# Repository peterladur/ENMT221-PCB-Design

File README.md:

# ENMT221-PCB-Design
PCB Design for my line following robot for ENMT221

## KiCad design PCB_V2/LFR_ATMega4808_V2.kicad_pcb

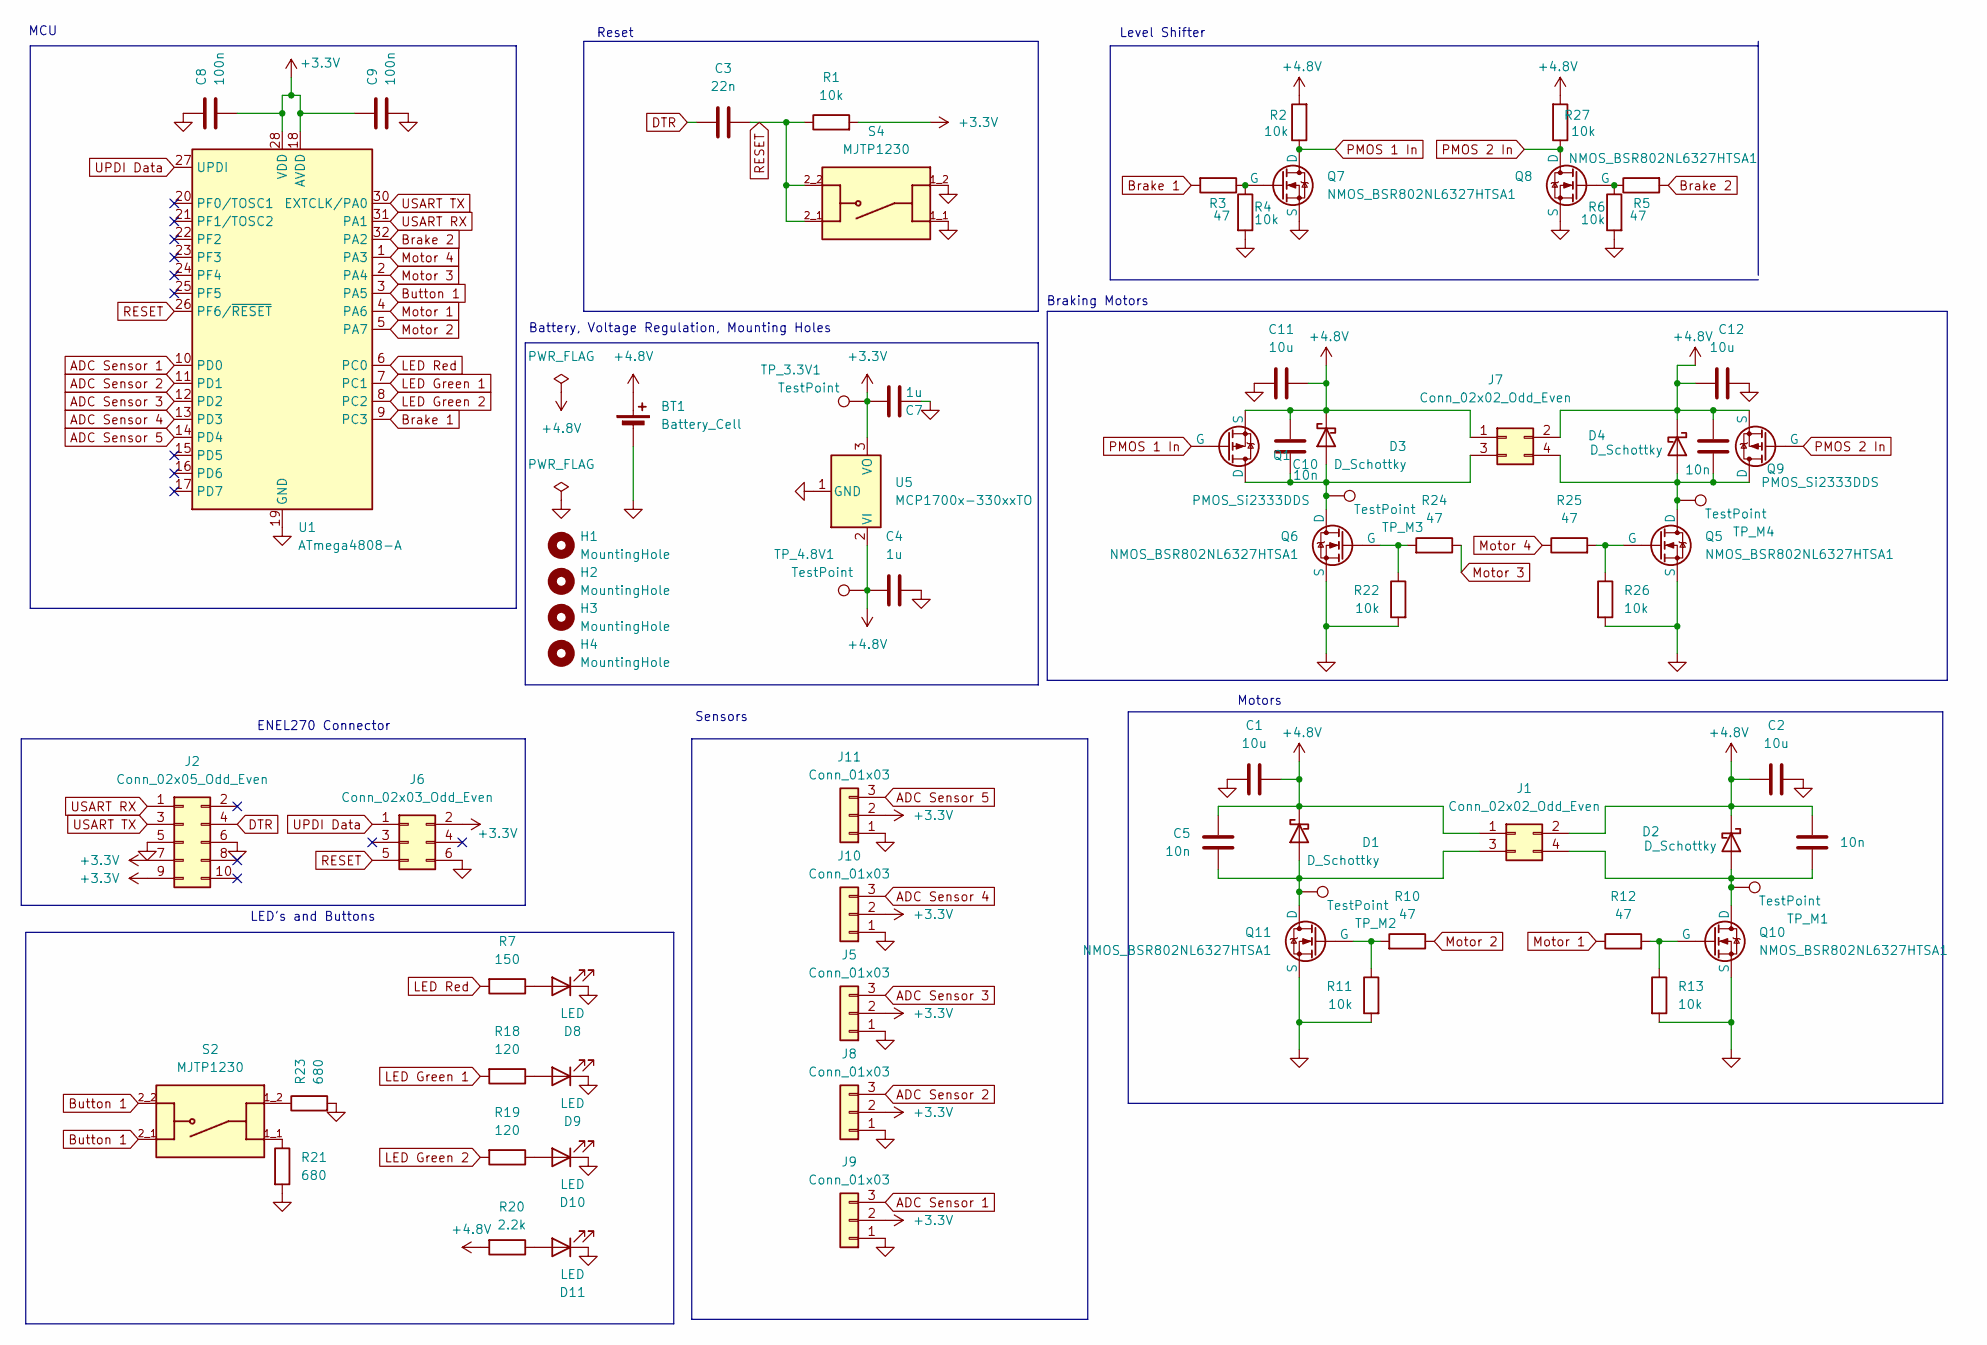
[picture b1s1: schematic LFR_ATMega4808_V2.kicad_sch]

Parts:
BT1: Battery_Cell; PinHeader_1x02_P2.54mm_Vertical
C1, C2, C11, C12: 10u; C_Radial_D6.3mm_H5.0mm_P2.50mm
C3: 22n; C_0805_2012Metric_Pad1.18x1.45mm_HandSolder
C4, C7: 1u; C_Radial_D6.3mm_H5.0mm_P2.50mm
C5, C6, C10, C13: 10n; C_0805_2012Metric_Pad1.18x1.45mm_HandSolder
C8, C9: 100n; C_0805_2012Metric_Pad1.18x1.45mm_HandSolder
D1, D2, D3, D4: D_Schottky; D_SMA
D8, D9, D10, D11: LED; LED_D5.0mm
H1, H2, H3, H4: MountingHole; MountingHole_2.2mm_M2_Pad
J1, J7: Conn_02x02_Odd_Even; PinHeader_2x02_P2.54mm_Vertical
J2: Conn_02x05_Odd_Even; PinHeader_2x05_P2.54mm_Vertical
J5, J8, J9, J10, J11: Conn_01x03; PinHeader_1x03_P2.54mm_Vertical
J6: Conn_02x03_Odd_Even; PinHeader_2x03_P2.54mm_Vertical
Q1: PMOS_Si2333DDS; SOT-23-3
Q5, Q6, Q7, Q8, Q10, Q11: NMOS_BSR802NL6327HTSA1; SOT-23-3
Q9: PMOS_Si2333DDS; SOT-23
R1, R2, R4, R6, R11, R13, R22, R26, R27: 10k; R_0805_2012Metric_Pad1.20x1.40mm_HandSolder
R3, R5, R10, R12, R24, R25: 47; R_0805_2012Metric_Pad1.20x1.40mm_HandSolder
R7: 150; R_0805_2012Metric_Pad1.20x1.40mm_HandSolder
R18, R19: 120; R_0805_2012Metric_Pad1.20x1.40mm_HandSolder
R20: 2.2k; R_0805_2012Metric_Pad1.20x1.40mm_HandSolder
R21, R23: 680; R_0805_2012Metric_Pad1.20x1.40mm_HandSolder
S2, S4: MJTP1230; Switch_Tactile_THT_6x6mm_MJTP1230; PARTREV NA
TP_3.3V1, TP_4.8V1: TestPoint; TestPoint_Pad_D1.0mm
TP_M1, TP_M2, TP_M3, TP_M4: TestPoint; TestPoint_Pad_D1.0mm
U1: ATmega4808-A; TQFP-32_7x7mm_P0.8mm
U5: MCP1700x-330xxTO; TO-92_Inline

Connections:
+3.3V: C7.1, C8.2, C9.1, J2.7, J2.9, J5.2, J6.2, J8.2, J9.2, J10.2, J11.2, R1.2, TP_3.3V1.1 (1_1), U1.18 (AVDD), U1.28 (VDD), U5.3 (VO)
+4.8V: BT1.1 (+), C1.2, C2.2, C4.1, C5.1, C6.1, C10.1, C11.2, C12.2, C13.1, D1.1 (K), D2.1 (K), D3.1 (K), D4.1 (K), J1.1, J1.2, J7.1, J7.2, Q1.2 (S), Q9.2 (S), R2.2, R20.2, R27.2, TP_4.8V1.1 (1_1), U5.2 (VI)
ADC Sensor 1: J9.3, U1.10 (PD0)
ADC Sensor 2: J8.3, U1.11 (PD1)
ADC Sensor 3: J5.3, U1.12 (PD2)
ADC Sensor 4: J10.3, U1.13 (PD3)
ADC Sensor 5: J11.3, U1.14 (PD4)
Brake 1: R3.2, U1.9 (PC3)
Brake 2: R5.2, U1.32 (PA2)
Button 1: S2.2_1, S2.2_2, U1.3 (PA5)
DTR: C3.1, J2.4
GND: BT1.2 (-), C1.1, C2.1, C4.2, C7.2, C8.1, C9.2, C11.1, C12.1, D8.1 (K), D9.1 (K), D10.1 (K), D11.1 (K), J2.5, J2.6, J5.1, J6.6, J8.1, J9.1, J10.1, J11.1, Q5.2 (S), Q6.2 (S), Q7.2 (S), Q8.2 (S), Q10.2 (S), Q11.2 (S), R4.2, R6.2, R11.2, R13.2, R21.2, R22.2, R23.2, R26.2, S4.1_1, S4.1_2, U1.19 (GND), U1.29 (GND), U5.1 (GND)
LED Green 1: R18.2, U1.7 (PC1)
LED Green 2: R19.2, U1.8 (PC2)
LED Red: R7.2, U1.6 (PC0)
Motor 1: R12.1, U1.4 (PA6)
Motor 2: R10.1, U1.5 (PA7)
Motor 3: R24.1, U1.2 (PA4)
Motor 4: R25.1, U1.1 (PA3)
unnamed: C5.2, D1.2 (A), J1.3, Q11.3 (D), TP_M2.1 (1_1)
unnamed: C6.2, D2.2 (A), J1.4, Q10.3 (D), TP_M1.1 (1_1)
unnamed: C10.2, D3.2 (A), J7.3, Q1.3 (D), Q6.3 (D), TP_M3.1 (1_1)
unnamed: C13.2, D4.2 (A), J7.4, Q5.3 (D), Q9.3 (D), TP_M4.1 (1_1)
unnamed: D8.2 (A), R7.1
unnamed: D9.2 (A), R18.1
unnamed: D10.2 (A), R19.1
unnamed: D11.2 (A), R20.1
unnamed: Q5.1 (G), R25.2, R26.1
unnamed: Q6.1 (G), R22.1, R24.2
unnamed: Q7.1 (G), R3.1, R4.1
unnamed: Q8.1 (G), R5.1, R6.1
unnamed: Q10.1 (G), R12.2, R13.1
unnamed: Q11.1 (G), R10.2, R11.1
unnamed: R21.1, S2.1_1
unnamed: R23.1, S2.1_2
PMOS 1 In: Q1.1 (G), Q7.3 (D), R2.1
PMOS 2 In: Q8.3 (D), Q9.1 (G), R27.1
RESET: C3.2, J6.5, R1.1, S4.2_1, S4.2_2, U1.26 (PF6/~RESET)
UPDI Data: J6.1, U1.27 (UPDI)
USART RX: J2.1, U1.31 (PA1)
USART TX: J2.3, U1.30 (EXTCLK/PA0)

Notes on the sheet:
LED's and Buttons
Level Shifter
ENEL270 Connector
MCU
Battery, Voltage Regulation, Mounting Holes
Reset
Sensors
Motors
Braking Motors

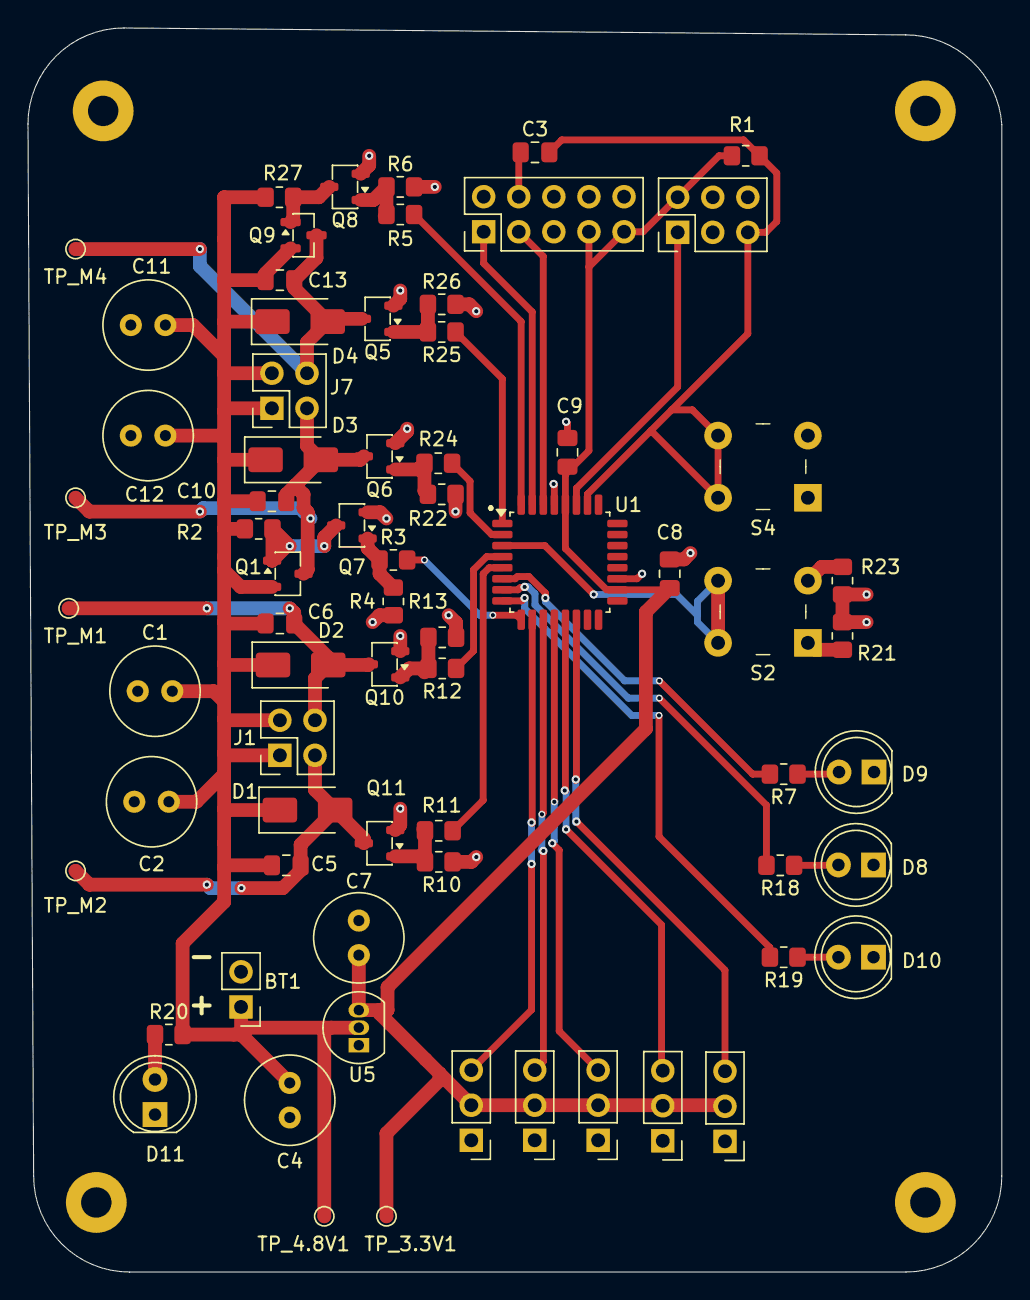
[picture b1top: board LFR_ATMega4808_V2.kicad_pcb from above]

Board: 2 copper layers, 70.5 x 90.0 mm, 74 parts (0 on the bottom side), 41 nets.

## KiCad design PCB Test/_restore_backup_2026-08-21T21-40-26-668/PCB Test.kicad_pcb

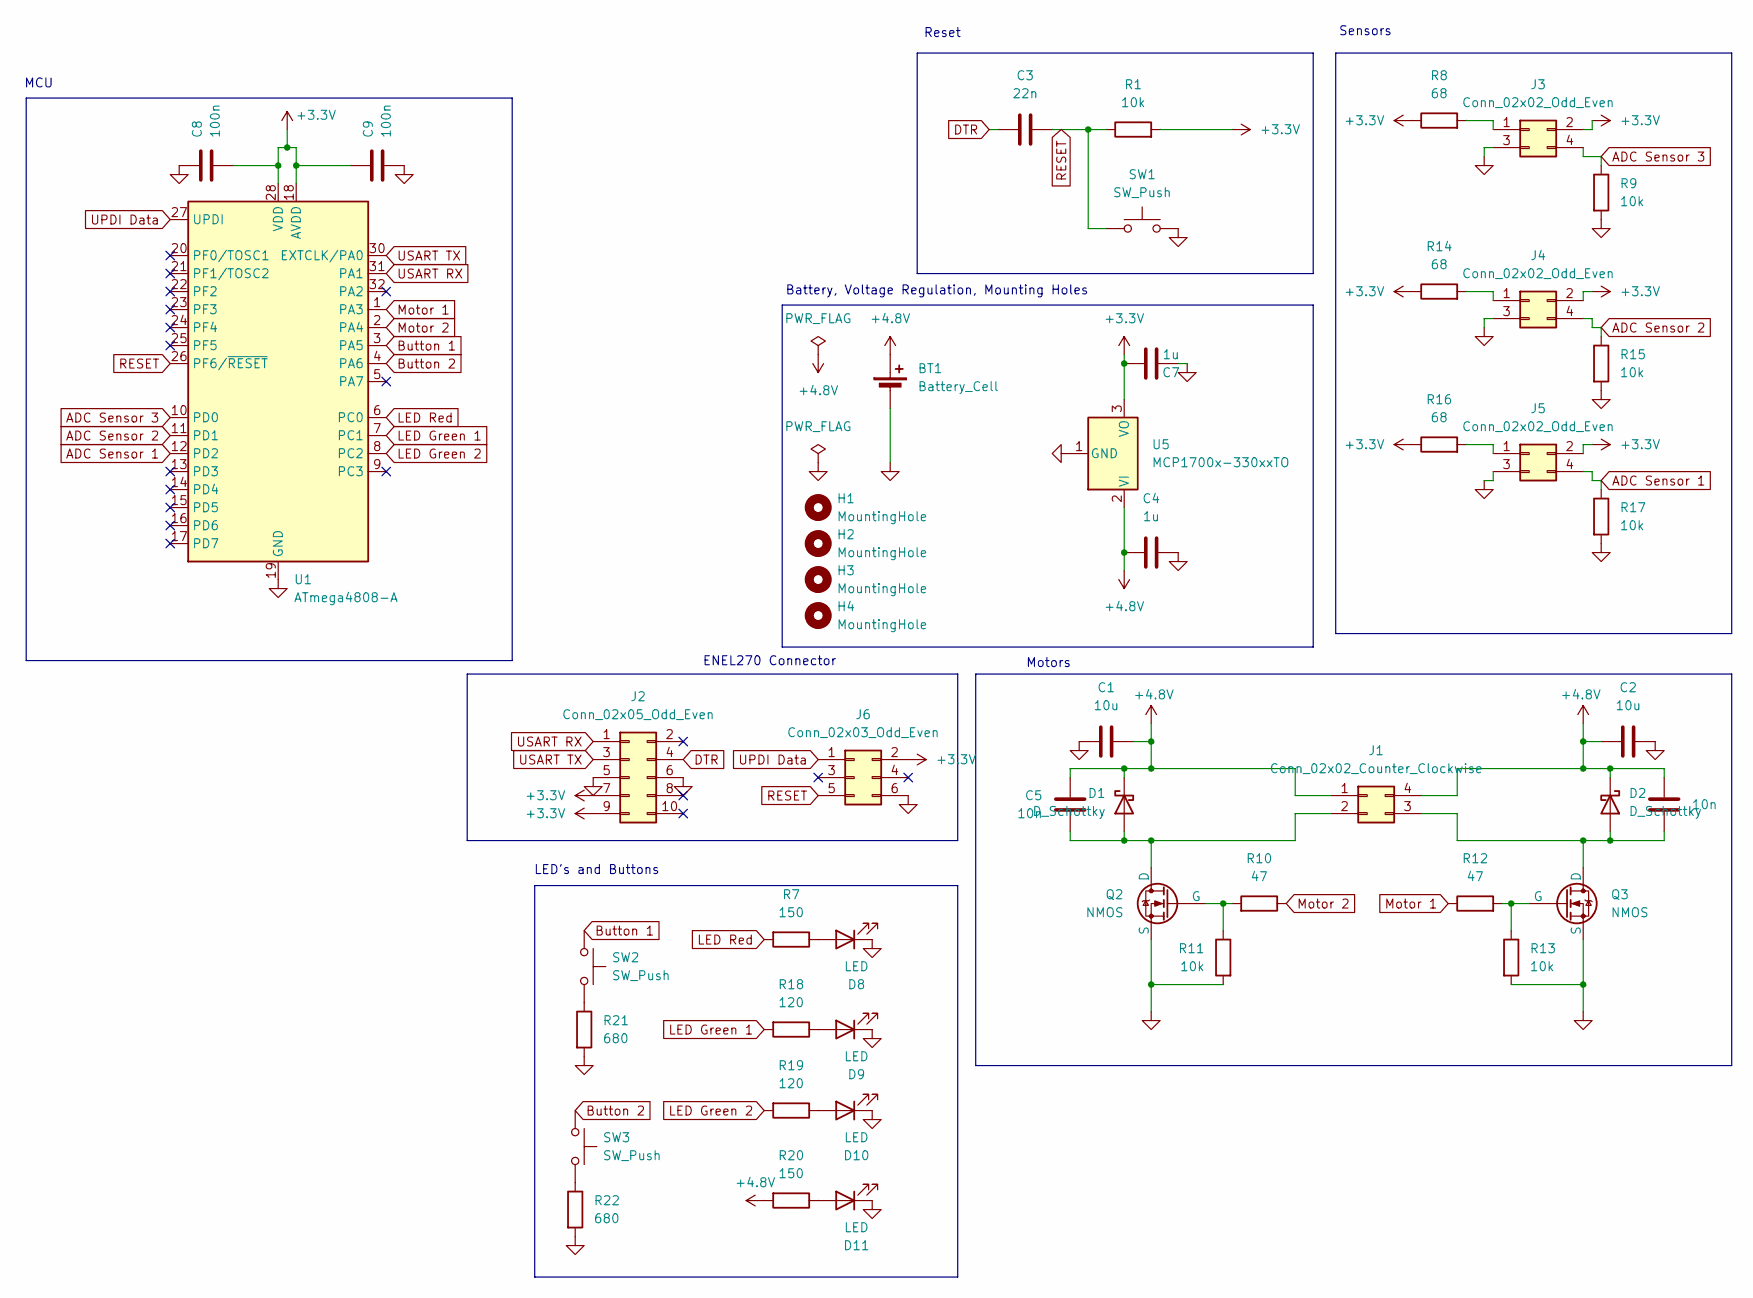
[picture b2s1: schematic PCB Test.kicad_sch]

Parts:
BT1: Battery_Cell; PinSocket_1x02_P1.00mm_Vertical_SMD_Pin1Left
C1, C2: 10u; C_Radial_D6.3mm_H5.0mm_P2.50mm
C3: 22n; C_0805_2012Metric_Pad1.18x1.45mm_HandSolder
C4, C7: 1u; C_Radial_D6.3mm_H5.0mm_P2.50mm
C5, C6: 10n; C_0805_2012Metric_Pad1.18x1.45mm_HandSolder
C8, C9: 100n; C_0805_2012Metric_Pad1.18x1.45mm_HandSolder
D1, D2: D_Schottky; D_SMA
D8, D9, D10, D11: LED; LED_D5.0mm
H1, H2, H3, H4: MountingHole; MountingHole_2.2mm_M2
J1: Conn_02x02_Counter_Clockwise; NS-Tech_Grove_1x04_P2mm_Vertical
J2: Conn_02x05_Odd_Even; PinHeader_2x05_P2.54mm_Vertical
J3, J4, J5: Conn_02x02_Odd_Even; Harwin_LTek-Male_2x02_P2.00mm_Vertical
J6: Conn_02x03_Odd_Even; PinHeader_2x03_P2.54mm_Vertical
Q2, Q3: NMOS; SOT-23
R1, R9, R11, R13, R15, R17: 10k; R_0805_2012Metric_Pad1.20x1.40mm_HandSolder
R7, R20: 150; R_0805_2012Metric_Pad1.20x1.40mm_HandSolder
R8, R14, R16: 68; R_0805_2012Metric_Pad1.20x1.40mm_HandSolder
R10, R12: 47; R_0805_2012Metric_Pad1.20x1.40mm_HandSolder
R18, R19: 120; R_0805_2012Metric_Pad1.20x1.40mm_HandSolder
R21, R22: 680; R_0805_2012Metric_Pad1.20x1.40mm_HandSolder
SW1, SW2, SW3: SW_Push; SW_PUSH_1P1T_6x3.5mm_H4.3_APEM_MJTP1243
U1: ATmega4808-A; TQFP-32_7x7mm_P0.8mm
U5: MCP1700x-330xxTO; TO-92_Inline

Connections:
+3.3V: C7.1, C8.2, C9.1, J2.7, J2.9, J3.2, J4.2, J5.2, J6.2, R1.2, R8.1, R14.1, R16.1, U1.18 (AVDD), U1.28 (VDD), U5.3 (VO)
+4.8V: BT1.1 (+), C1.2, C2.2, C4.1, C5.1, C6.1, D1.1 (K), D2.1 (K), J1.1, J1.4, R20.2, U5.2 (VI)
ADC Sensor 1: J5.4, R17.1, U1.12 (PD2)
ADC Sensor 2: J4.4, R15.1, U1.11 (PD1)
ADC Sensor 3: J3.4, R9.1, U1.10 (PD0)
Button 1: SW2.1, U1.3 (PA5)
Button 2: SW3.1, U1.4 (PA6)
DTR: C3.1, J2.4
GND: BT1.2 (-), C1.1, C2.1, C4.2, C7.2, C8.1, C9.2, D8.1 (K), D9.1 (K), D10.1 (K), D11.1 (K), J2.5, J2.6, J3.3, J4.3, J5.3, J6.6, Q2.3 (S), Q3.3 (S), R9.2, R11.2, R13.2, R15.2, R17.2, R21.2, R22.2, SW1.2, U1.19 (GND), U1.29 (GND), U5.1 (GND)
LED Green 1: R18.2, U1.7 (PC1)
LED Green 2: R19.2, U1.8 (PC2)
LED Red: R7.2, U1.6 (PC0)
Motor 1: R12.1, U1.1 (PA3)
Motor 2: R10.1, U1.2 (PA4)
unnamed: C5.2, D1.2 (A), J1.2, Q2.1 (D)
unnamed: C6.2, D2.2 (A), J1.3, Q3.1 (D)
unnamed: D8.2 (A), R7.1
unnamed: D9.2 (A), R18.1
unnamed: D10.2 (A), R19.1
unnamed: D11.2 (A), R20.1
unnamed: J3.1, R8.2
unnamed: J4.1, R14.2
unnamed: J5.1, R16.2
unnamed: Q2.2 (G), R10.2, R11.1
unnamed: Q3.2 (G), R12.2, R13.1
unnamed: R21.1, SW2.2
unnamed: R22.1, SW3.2
RESET: C3.2, J6.5, R1.1, SW1.1, U1.26 (PF6/~RESET)
UPDI Data: J6.1, U1.27 (UPDI)
USART RX: J2.1, U1.31 (PA1)
USART TX: J2.3, U1.30 (EXTCLK/PA0)

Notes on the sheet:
LED's and Buttons
ENEL270 Connector
MCU
Battery, Voltage Regulation, Mounting Holes
Reset
Sensors
Motors

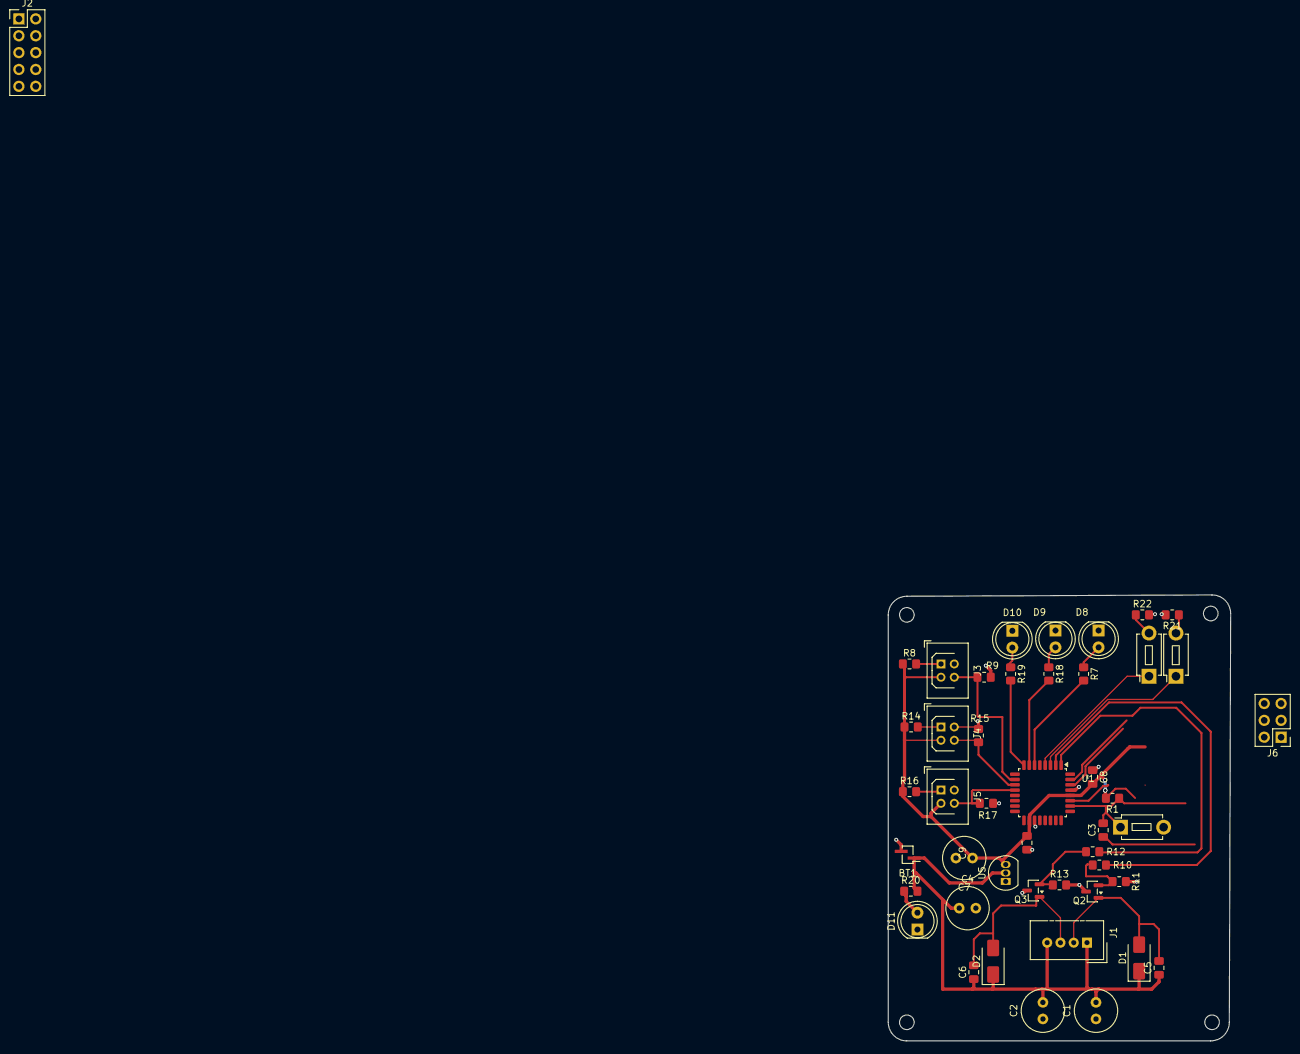
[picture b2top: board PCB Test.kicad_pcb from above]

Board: 2 copper layers, 51.6 x 67.2 mm, 50 parts (0 on the bottom side), 31 nets.
